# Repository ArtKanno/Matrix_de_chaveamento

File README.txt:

Projeto legal da matrix de chaveamento

teste do git

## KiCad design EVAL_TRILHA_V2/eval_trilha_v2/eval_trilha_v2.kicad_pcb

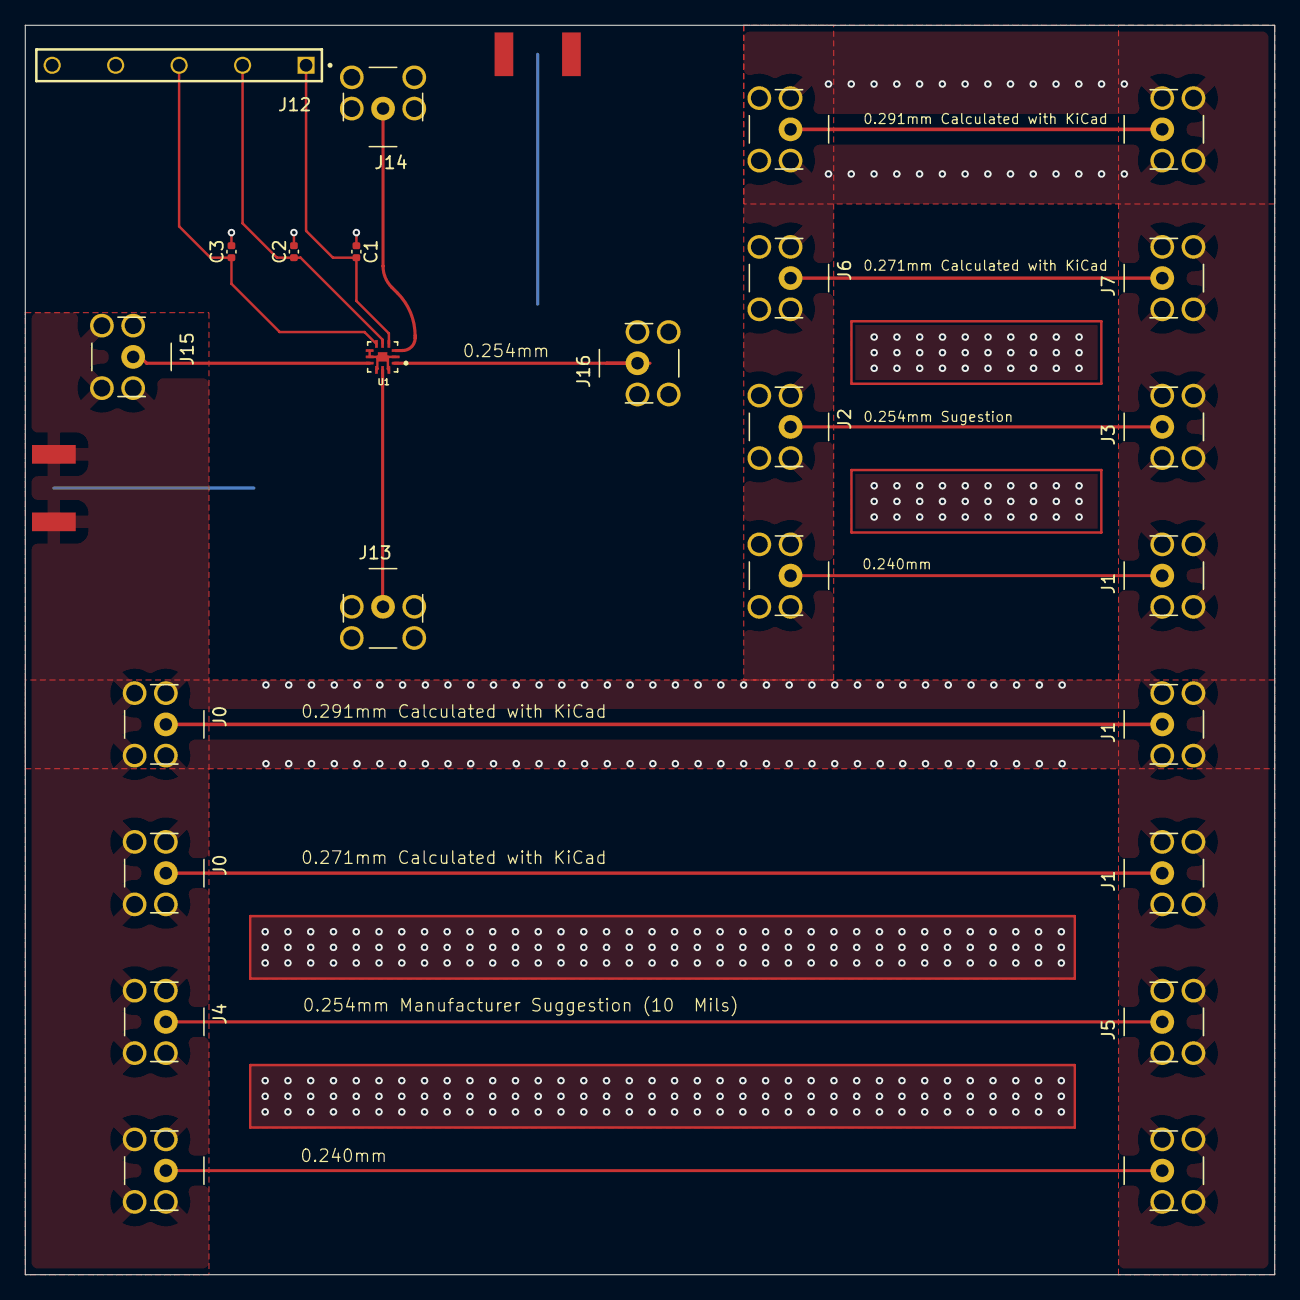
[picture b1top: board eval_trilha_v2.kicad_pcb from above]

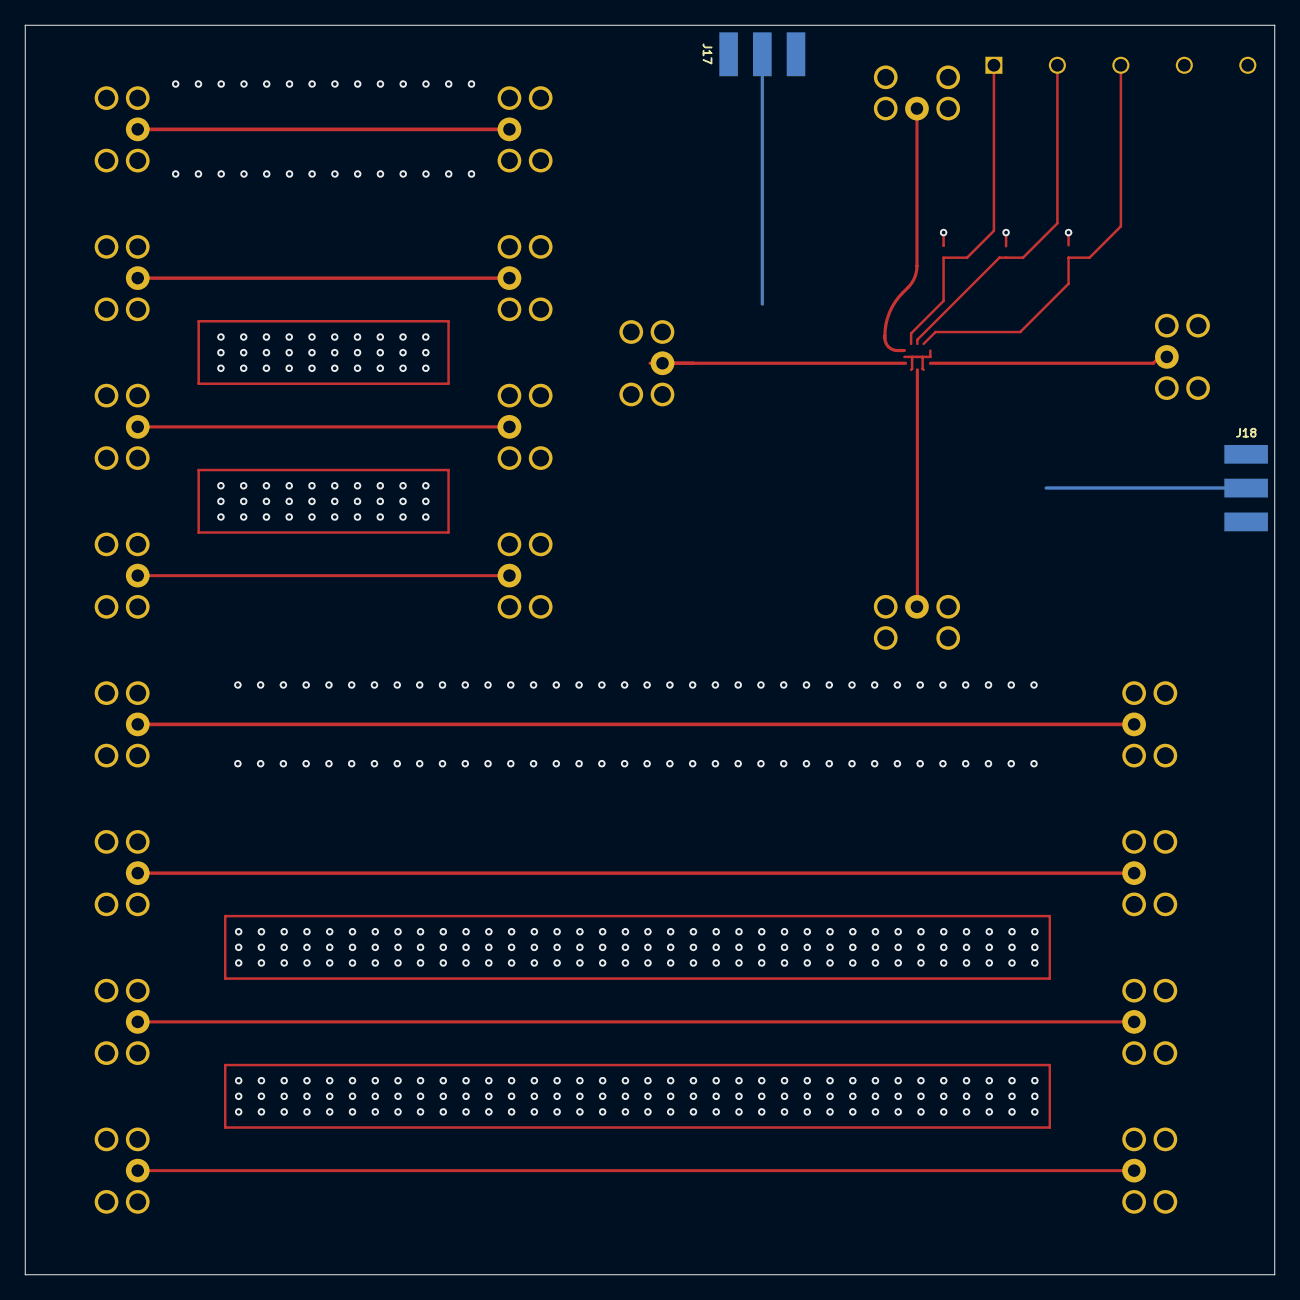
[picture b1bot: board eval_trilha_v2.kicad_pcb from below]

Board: 4 copper layers, 100.0 x 100.0 mm, 27 parts (2 on the bottom side), 14 nets.

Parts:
C1, C2, C3: C; C_0402_1005Metric
J0, J0#2, J1, J1#2, J1#3, J2, J3, J4, J5, J6, J7, J8, J8#2, J9, J10, J11, J13, J14, J15, J16: 0732511352; Footprint_adaptado
J12: TSW-205-14-L-S; SAMTEC_TSW-205-14-L-S
J17, J18: CON-SMA-EDGE-S; RFSOLUTIONS_CON-SMA-EDGE-S
U1: SKY13373-460LF; QFN50P200X200X65-13N

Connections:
/Ctrl1: C1.2, J12.01, U1.4 (V1)
/Ctrl2: C2.1, J12.02, U1.5 (V2)
/RF1: J16.1, U1.1 (J1)
/RF2: J15.1, U1.9 (J2)
/RF3: J14.1, U1.3 (J3)
GND: C1.1, C2.2, C3.2, J0.S1, J0.S2, J0.S3, J0.S4, J0#2.S1, J0#2.S2, J0#2.S3, J0#2.S4, J1.S1, J1.S2, J1.S3, J1.S4, J1#2.S1, J1#2.S2, J1#2.S3, J1#2.S4, J1#3.S1, J1#3.S2, J1#3.S3, J1#3.S4, J2.S1, J2.S2, J2.S3, J2.S4, J3.S1, J3.S2, J3.S3, J3.S4, J4.S1, J4.S2, J4.S3, J4.S4, J5.S1, J5.S2, J5.S3, J5.S4, J6.S1, J6.S2, J6.S3, J6.S4, J7.S1, J7.S2, J7.S3, J7.S4, J8.S1, J8.S2, J8.S3, J8.S4, J8#2.S1, J8#2.S2, J8#2.S3, J8#2.S4, J9.S1, J9.S2, J9.S3, J9.S4, J10.S1, J10.S2, J10.S3, J10.S4, J11.S1, J11.S2, J11.S3, J11.S4, J12.04, J13.S1, J13.S2, J13.S3, J13.S4, J14.S1, J14.S2, J14.S3, J14.S4, J15.S1, J15.S2, J15.S3, J15.S4, J16.S1, J16.S2, J16.S3, J16.S4, J17.G1, J17.G2, J17.G3, J17.G4, J18.G1, J18.G2, J18.G3, J18.G4, U1.2 (GND), U1.7 (GND), U1.8 (GND), U1.10 (GND), U1.12 (GND), U1.13 (GND)
unnamed: J0.1, J1#2.1
unnamed: J2.1, J3.1
unnamed: J4.1, J5.1
unnamed: J6.1, J7.1
unnamed: J8.1, J9.1
unnamed: J10.1, J11.1
unnamed: J13.1, U1.11 (RFC)
VDD: C3.1, J12.03, U1.6 (VDD)

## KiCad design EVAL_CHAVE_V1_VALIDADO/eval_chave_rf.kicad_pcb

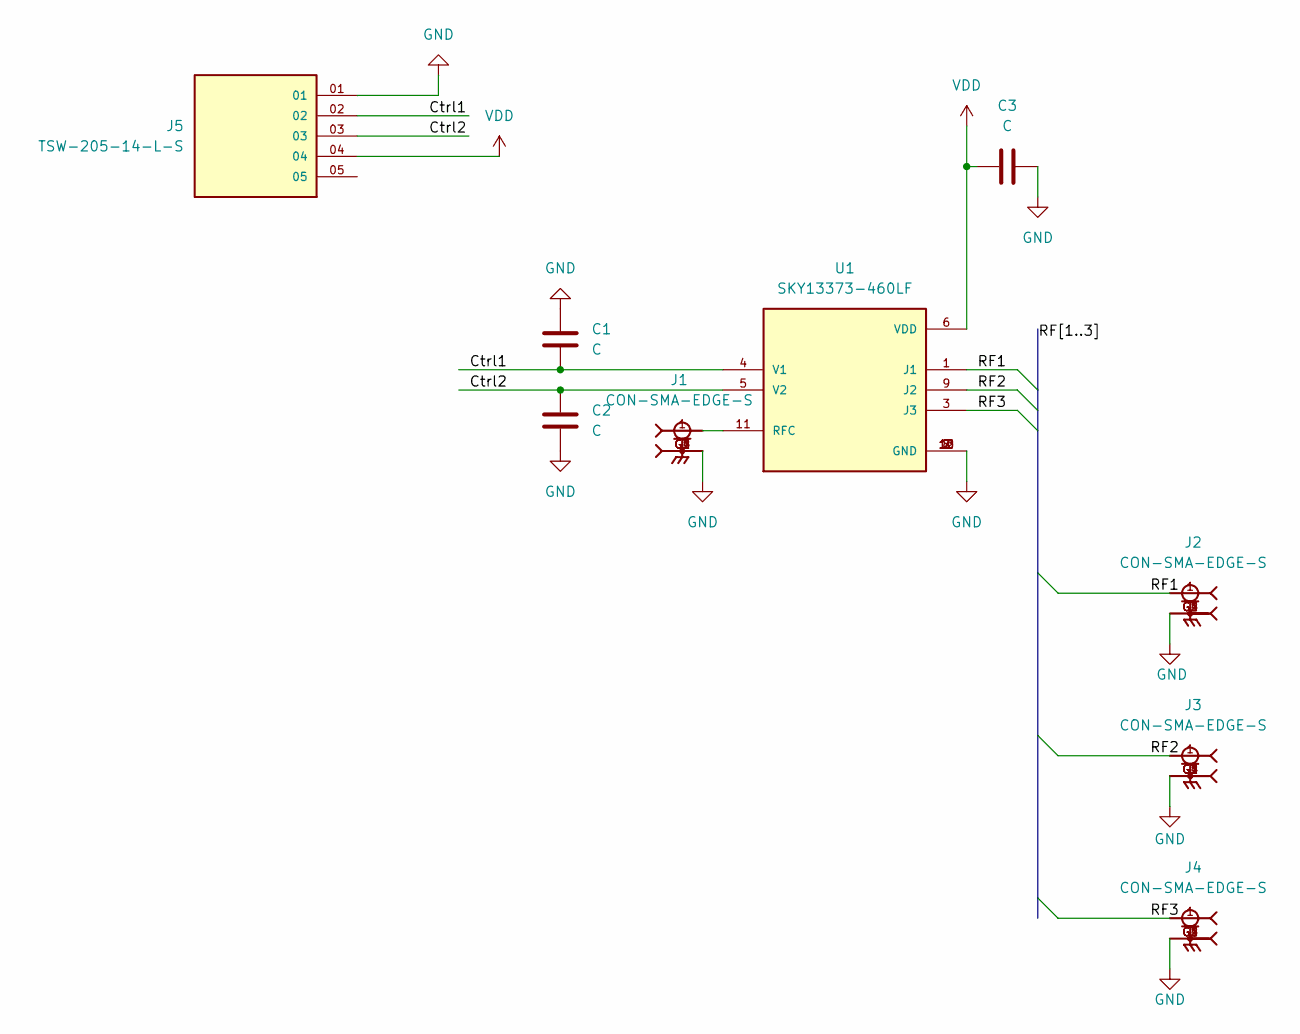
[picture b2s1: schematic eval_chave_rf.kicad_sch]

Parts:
C1, C2, C3: C; C_0402_1005Metric
J1, J2, J3, J4: CON-SMA-EDGE-S; RFSOLUTIONS_CON-SMA-EDGE-S; PARTREV 1
J5: TSW-205-14-L-S; SAMTEC_TSW-205-14-L-S; PARTREV R
U1: SKY13373-460LF; QFN50P200X200X65-13N; PARTREV May 6, 2016

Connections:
/Ctrl1: C1.2, J5.02, U1.4 (V1)
/Ctrl2: C2.1, J5.03, U1.5 (V2)
/RF1: J2.1, U1.1 (J1)
/RF2: J3.1, U1.9 (J2)
/RF3: J4.1, U1.3 (J3)
GND: C1.1, C2.2, C3.2, J1.G1, J1.G2, J1.G3, J1.G4, J2.G1, J2.G2, J2.G3, J2.G4, J3.G1, J3.G2, J3.G3, J3.G4, J4.G1, J4.G2, J4.G3, J4.G4, J5.01, U1.2 (GND), U1.7 (GND), U1.8 (GND), U1.10 (GND), U1.12 (GND), U1.13 (GND)
unnamed: J1.1, U1.11 (RFC)
VDD: C3.1, J5.04, U1.6 (VDD)

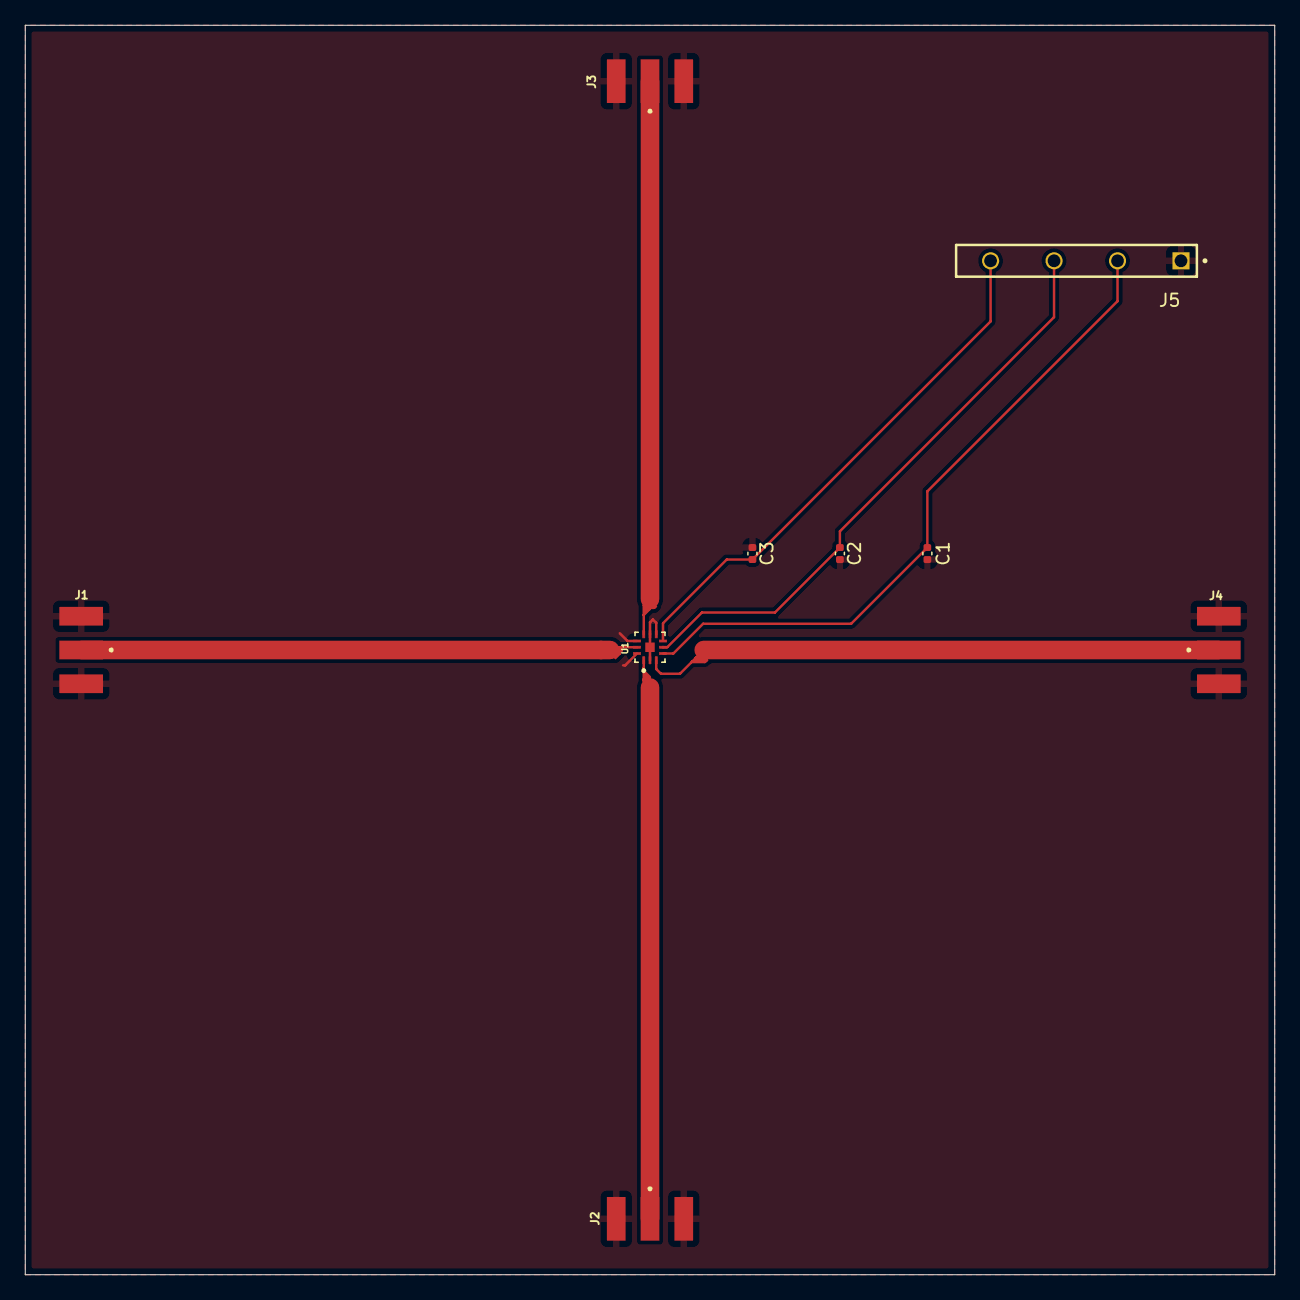
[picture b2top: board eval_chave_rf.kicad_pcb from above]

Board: 2 copper layers, 100.0 x 100.0 mm, 9 parts (0 on the bottom side), 8 nets.

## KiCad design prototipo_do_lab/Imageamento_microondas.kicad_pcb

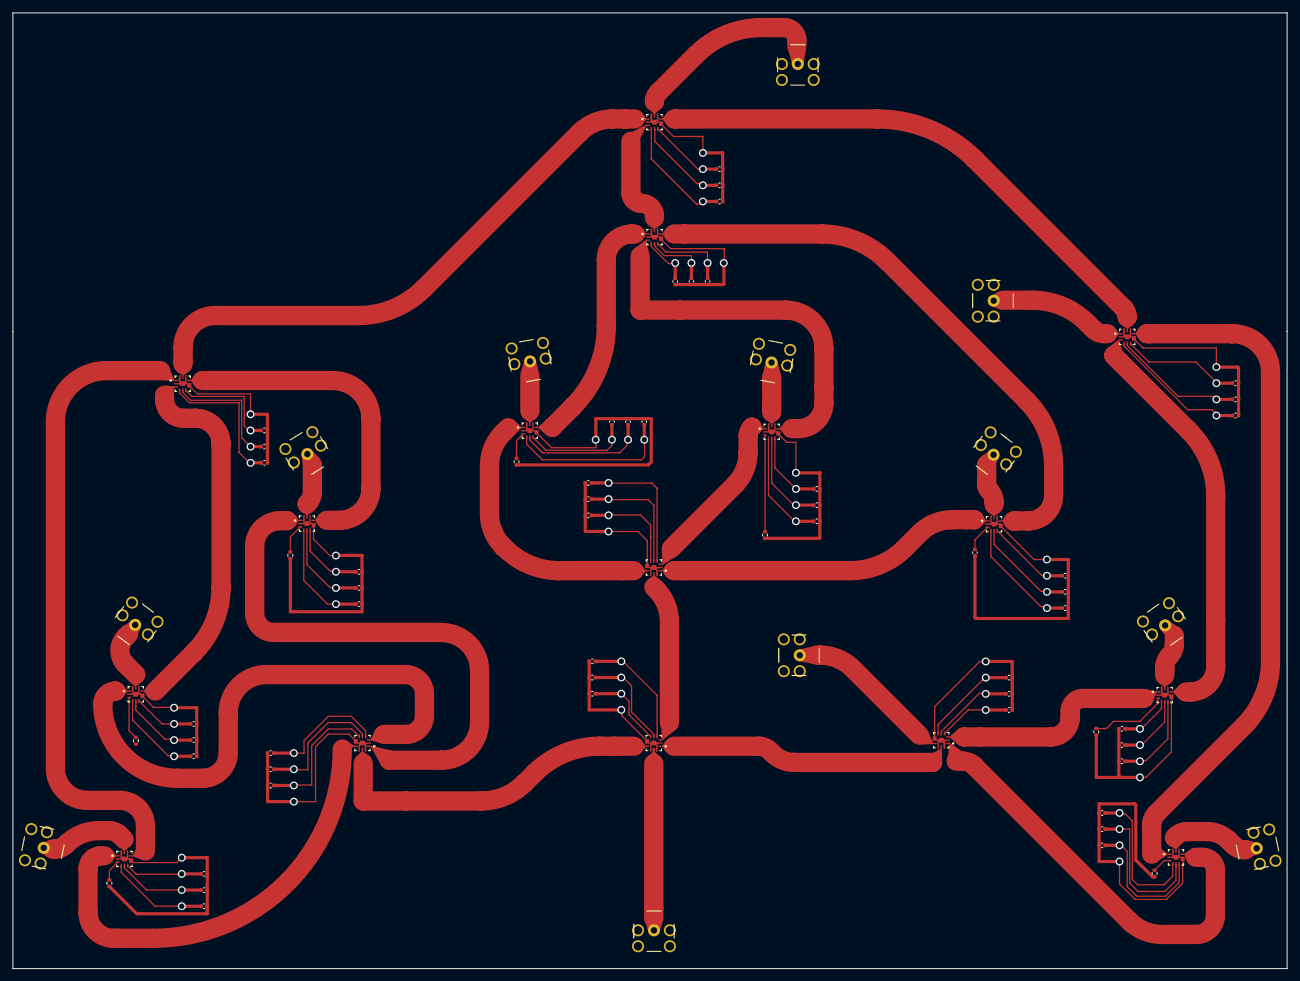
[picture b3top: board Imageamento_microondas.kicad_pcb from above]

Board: 2 copper layers, 200.0 x 150.0 mm, 84 parts (0 on the bottom side), 76 nets.

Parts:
C1, C2, C3, C4, C5, C6, C7, C8, C9, C10, C11, C12, C13, C14, C15, C16, C17, C18, C19, C20, C21, C22, C23, C24, C25, C26, C27, C28, C29, C30, C31, C32, C33, C34, C35, C36, C37, C38, C39, C40, C41, C42, C43, C44, C45, C46, C47, C48: C; C_0402_1005Metric
J1, J2, J3, J4, J5, J6, J7, J8, J9, J10, J12, J13: 0732511352; Footprint_adaptado
R1, R2, R3, R4, R5, R7, R8: R; R_0402_1005Metric
R6: R; C_0402_1005Metric
U1, U2, U3, U4, U5, U6, U7, U8, U9, U10, U11, U12, U13, U14, U15, U16: SKY13373-460LF; QFN50P200X200X65-13N_1LabProt

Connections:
/CA_1: C27.2, U5.4 (V1)
/CA_2: C28.1, U5.5 (V2)
/CA_3: C29.2, U6.4 (V1)
/CA_4: C30.1, U6.5 (V2)
/CA_5: C31.2, U7.4 (V1)
/CA_6: C32.1, U7.5 (V2)
/CA_7: C37.2, U8.4 (V1)
/CA_8: C38.1, U8.5 (V2)
/CA_9: C35.2, U9.4 (V1)
/CA_10: C36.1, U9.5 (V2)
/CA_11: C33.2, U10.4 (V1)
/CA_12: C34.1, U10.5 (V2)
/CA_13: C39.2, U11.4 (V1)
/CA_14: C40.1, U11.5 (V2)
/CA_15: C41.2, U12.4 (V1)
/CA_16: C42.1, U12.5 (V2)
/CE1_1: C1.2, U1.4 (V1)
/CE1_2: C2.1, U1.5 (V2)
/CE2_1: C3.2, U2.4 (V1)
/CE2_2: C4.1, U2.5 (V2)
/CE2_3: C5.2, U3.4 (V1)
/CE2_4: C6.1, U3.5 (V2)
/CE2_5: C7.2, U4.4 (V1)
/CE2_6: C8.1, U4.5 (V2)
/CR1_1: C9.2, U13.4 (V1)
/CR1_2: C10.1, U13.5 (V2)
/CR2_1: C11.2, U14.4 (V1)
/CR2_2: C12.1, U14.5 (V2)
/CR2_3: C13.2, U15.4 (V1)
/CR2_4: C14.1, U15.5 (V2)
/CR2_5: C15.2, U16.4 (V1)
/CR2_6: C16.1, U16.5 (V2)
/E1_1: U1.9 (J2), U2.11 (RFC)
/E1_2: U1.3 (J3), U3.11 (RFC)
/E1_3: U1.1 (J1), U4.11 (RFC)
/E2_1: U2.1 (J1), U5.1 (J1)
/E2_2: U2.9 (J2), U6.1 (J1)
/E2_3: U2.3 (J3), U7.1 (J1)
/E2_4: U3.1 (J1), U8.1 (J1)
/E2_5: U3.9 (J2), U9.1 (J1)
/E2_6: U3.3 (J3), U10.1 (J1)
/E2_7: U4.1 (J1), U11.9 (J2)
/E2_8: U4.3 (J3), U12.1 (J1)
/R1_1: U13.1 (J1), U14.11 (RFC)
/R1_2: U13.3 (J3), U15.11 (RFC)
/R1_3: U13.9 (J2), U16.11 (RFC)
/R2_1: U5.9 (J2), U14.9 (J2)
/R2_2: U6.9 (J2), U14.1 (J1)
/R2_3: U7.9 (J2), U14.3 (J3)
/R2_4: U8.9 (J2), U15.9 (J2)
/R2_5: U9.9 (J2), U15.1 (J1)
/R2_6: U10.9 (J2), U15.3 (J3)
/R2_7: U11.1 (J1), U16.9 (J2)
/R2_8: U12.9 (J2), U16.3 (J3)
/segunda_camada_emissao/EXT_E: J10.1, U4.9 (J2)
/segunda_camada_recepcao/EXT_R: J13.1, U16.1 (J1)
GND: C1.1, C2.2, C3.1, C4.2, C5.1, C6.2, C7.1, C8.2, C9.1, C10.2, C11.1, C12.2, C13.1, C14.2, C15.1, C16.2, C17.2, C18.2, C19.2, C20.2, C21.2, C22.2, C23.2, C24.2, C25.2, C26.2, C27.1, C28.2, C29.1, C30.2, C31.1, C32.2, C33.1, C34.2, C35.1, C36.2, C37.1, C38.2, C39.1, C40.2, C41.1, C42.2, C43.2, C44.2, C45.2, C46.2, C47.2, C48.2, J1.S1, J1.S2, J1.S3, J1.S4, J2.S1, J2.S2, J2.S3, J2.S4, J3.S1, J3.S2, J3.S3, J3.S4, J4.S1, J4.S2, J4.S3, J4.S4, J5.S1, J5.S2, J5.S3, J5.S4, J6.S1, J6.S2, J6.S3, J6.S4, J7.S1, J7.S2, J7.S3, J7.S4, J8.S1, J8.S2, J8.S3, J8.S4, J9.S1, J9.S2, J9.S3, J9.S4, J10.S1, J10.S2, J10.S3, J10.S4, J12.S1, J12.S2, J12.S3, J12.S4, J13.S1, J13.S2, J13.S3, J13.S4, R1.2, R2.2, R3.2, R4.2, R5.2, R6.2, R7.2, R8.2, U1.2 (GND), U1.7 (GND), U1.8 (GND), U1.10 (GND), U1.12 (GND), U1.13 (GND), U2.2 (GND), U2.7 (GND), U2.8 (GND), U2.10 (GND), U2.12 (GND), U2.13 (GND), U3.2 (GND), U3.7 (GND), U3.8 (GND), U3.10 (GND), U3.12 (GND), U3.13 (GND), U4.2 (GND), U4.7 (GND), U4.8 (GND), U4.10 (GND), U4.12 (GND), U4.13 (GND), U5.2 (GND), U5.7 (GND), U5.8 (GND), U5.10 (GND), U5.12 (GND), U5.13 (GND), U6.2 (GND), U6.7 (GND), U6.8 (GND), U6.10 (GND), U6.12 (GND), U6.13 (GND), U7.2 (GND), U7.7 (GND), U7.8 (GND), U7.10 (GND), U7.12 (GND), U7.13 (GND), U8.2 (GND), U8.7 (GND), U8.8 (GND), U8.10 (GND), U8.12 (GND), U8.13 (GND), U9.2 (GND), U9.7 (GND), U9.8 (GND), U9.10 (GND), U9.12 (GND), U9.13 (GND), U10.2 (GND), U10.7 (GND), U10.8 (GND), U10.10 (GND), U10.12 (GND), U10.13 (GND), U11.2 (GND), U11.7 (GND), U11.8 (GND), U11.10 (GND), U11.12 (GND), U11.13 (GND), U12.2 (GND), U12.7 (GND), U12.8 (GND), U12.10 (GND), U12.12 (GND), U12.13 (GND), U13.2 (GND), U13.7 (GND), U13.8 (GND), U13.10 (GND), U13.12 (GND), U13.13 (GND), U14.2 (GND), U14.7 (GND), U14.8 (GND), U14.10 (GND), U14.12 (GND), U14.13 (GND), U15.2 (GND), U15.7 (GND), U15.8 (GND), U15.10 (GND), U15.12 (GND), U15.13 (GND), U16.2 (GND), U16.7 (GND), U16.8 (GND), U16.10 (GND), U16.12 (GND), U16.13 (GND)
unnamed: J8.1, U1.11 (RFC)
unnamed: R1.1, U5.3 (J3)
unnamed: J2.1, U5.11 (RFC)
unnamed: R2.1, U6.3 (J3)
unnamed: J1.1, U6.11 (RFC)
unnamed: R3.1, U7.3 (J3)
unnamed: J12.1, U7.11 (RFC)
unnamed: R6.1, U8.3 (J3)
unnamed: J5.1, U8.11 (RFC)
unnamed: R5.1, U9.3 (J3)
unnamed: J4.1, U9.11 (RFC)
unnamed: R4.1, U10.3 (J3)
unnamed: J3.1, U10.11 (RFC)
unnamed: R7.1, U11.3 (J3)
unnamed: J6.1, U11.11 (RFC)
unnamed: R8.1, U12.3 (J3)
unnamed: J7.1, U12.11 (RFC)
unnamed: J9.1, U13.11 (RFC)
VDD: C17.1, C18.1, C19.1, C20.1, C21.1, C22.1, C23.1, C24.1, C25.1, C26.1, C43.1, C44.1, C45.1, C46.1, C47.1, C48.1, U1.6 (VDD), U2.6 (VDD), U3.6 (VDD), U4.6 (VDD), U5.6 (VDD), U6.6 (VDD), U7.6 (VDD), U8.6 (VDD), U9.6 (VDD), U10.6 (VDD), U11.6 (VDD), U12.6 (VDD), U13.6 (VDD), U14.6 (VDD), U15.6 (VDD), U16.6 (VDD)
